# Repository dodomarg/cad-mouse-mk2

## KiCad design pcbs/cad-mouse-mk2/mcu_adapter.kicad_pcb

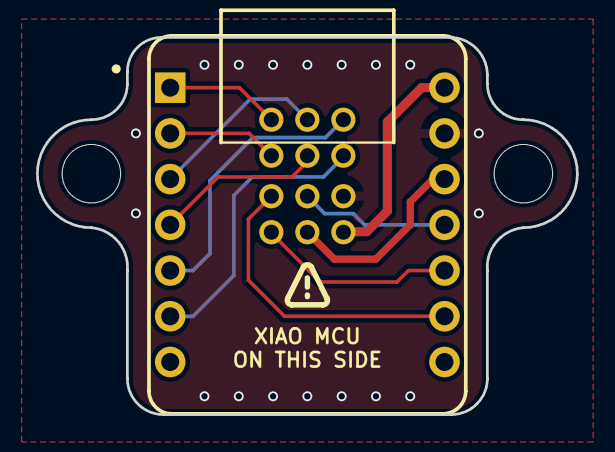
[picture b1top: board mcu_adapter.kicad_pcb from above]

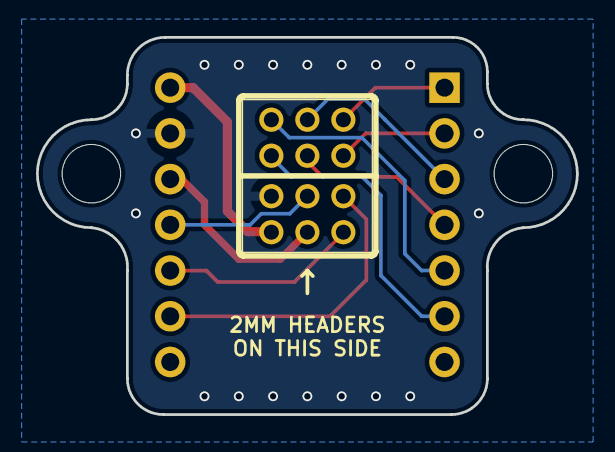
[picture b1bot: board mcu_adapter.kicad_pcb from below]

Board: 2 copper layers, 30.0 x 21.0 mm, 5 parts (2 on the bottom side), 12 nets.

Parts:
U1: XIAO-THRUHOLE; XIAO-GENERIC-THRUHOLE-MODULE14P-2.54-21X17.8MM_vf.79dh4xraR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
U$1, U$2: NRPN032PAEN-RC; CONN3X2_NRPN032PAEN-RC_vf.TnALXNQpQbKa17UGSM3jDw
UNK_HOLE_0: dummyfp0
UNK_HOLE_1: dummyfp1

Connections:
3V3: U1.12, U$2.3
5V: U1.14, U$2.1
D0: U1.1, U$1.6
D1: U1.2, U$1.5
D2: U1.3, U$1.4
D3: U1.4, U$1.3
D8: U1.9, U$2.6
D9: U1.10, U$2.5
D10: U1.11, U$2.4
GND: U1.13, U$2.2
SCL: U1.6, U$1.1
SDA: U1.5, U$1.2

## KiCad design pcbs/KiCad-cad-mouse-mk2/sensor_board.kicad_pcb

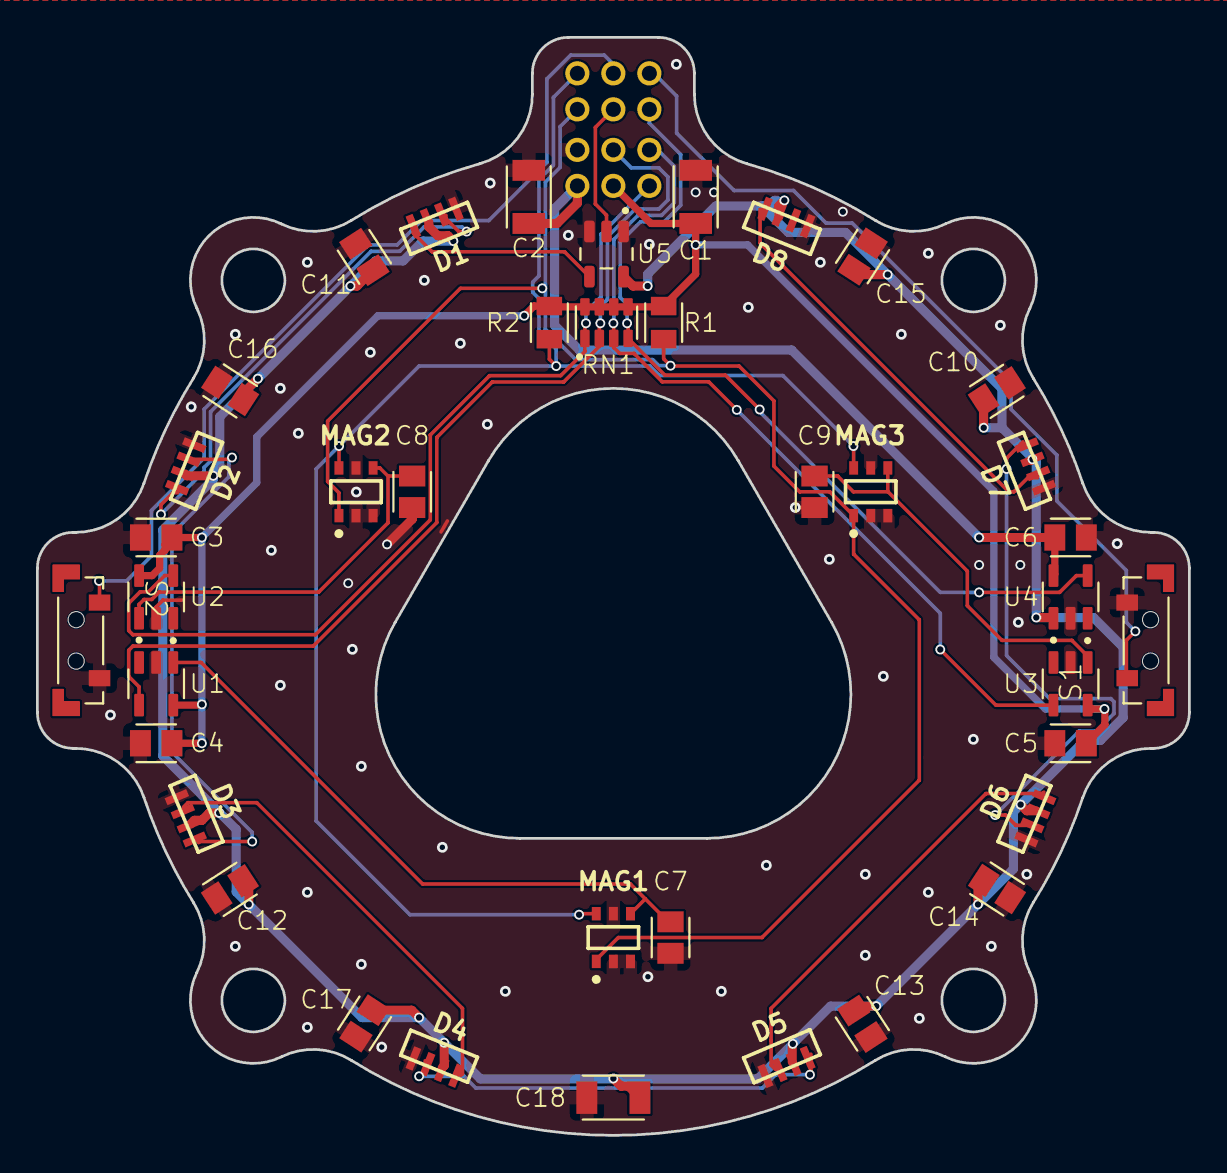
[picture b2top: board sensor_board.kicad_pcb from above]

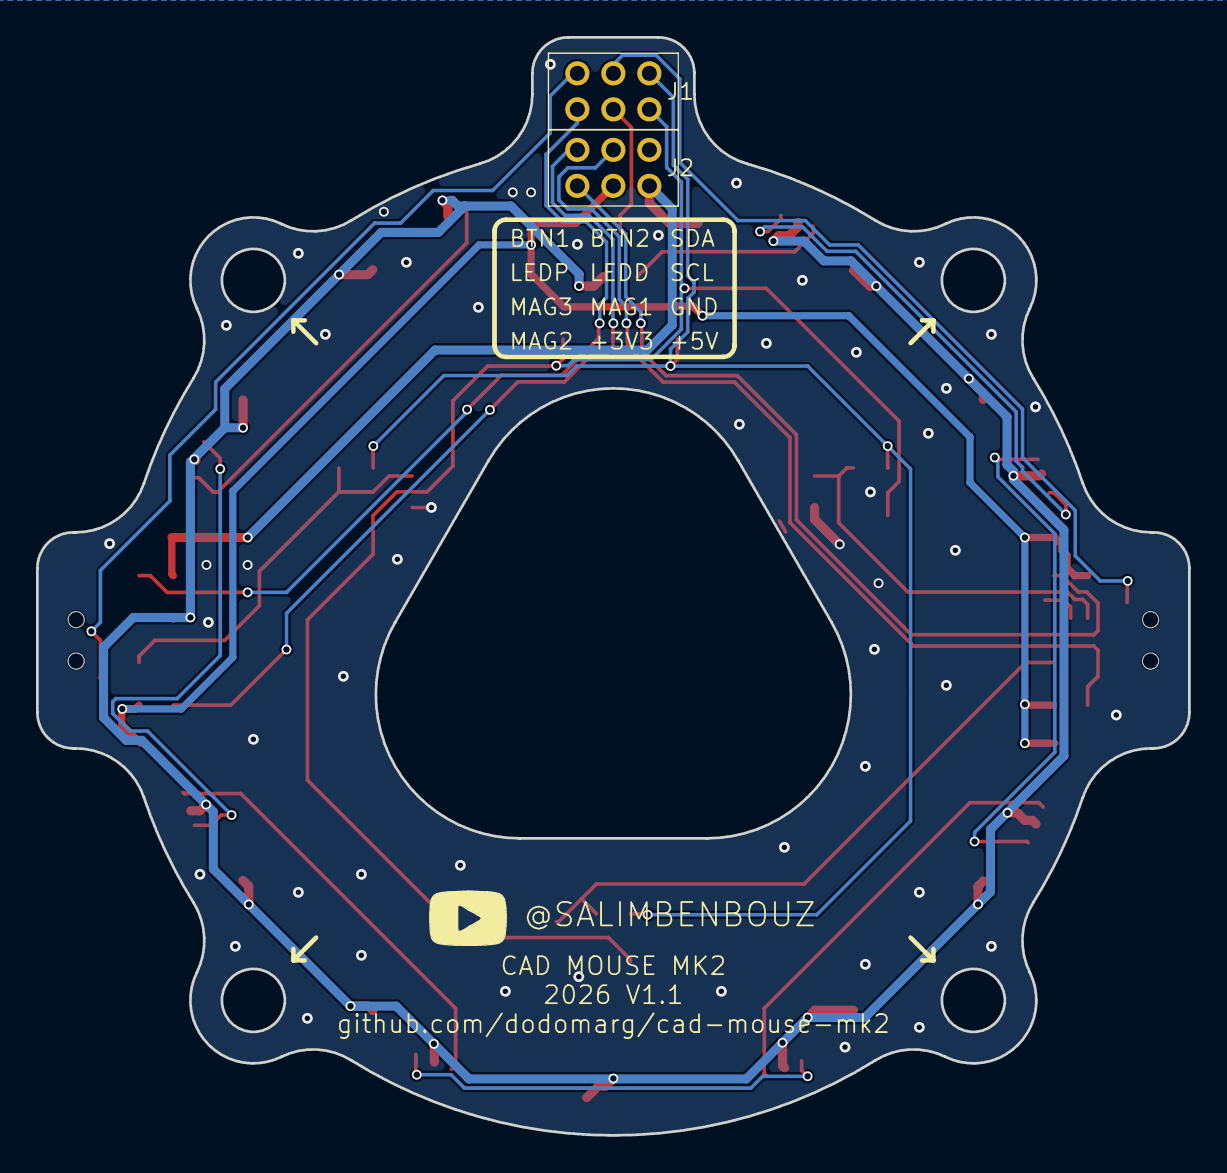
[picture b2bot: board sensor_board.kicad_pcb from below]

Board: 2 copper layers, 64.0 x 61.0 mm, 41 parts (2 on the bottom side), 24 nets.

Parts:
C1, C2: 1uF; CAPC3216X135_16290819
C3, C4, C5, C6, C7, C8, C9, C10, C11, C12, C13, C14, C15, C16, C17: 100nF; CAPC2012X110_16290819
C18: 22uF; CAPC3216X135_16290819
D1, D2, D3, D4, D5, D6, D7, D8: WS2812B-4020
J1, J2: CONN3X2_NPPN032AFCN-RC_SUL_vf.TnALXNQpQbKa17UGSM3jDw
MAG1, MAG2, MAG3: TLI493D-A2B6; SOP95P280X110-6N-V_vf.MgUPDs8QTrSiZWytZ2VEDw
R1, R2: 10K; RESC2012X65_16378527
RN1: 75R; RESCAF80P320X160X60-8N_vf.j0KZjKIVRhWMp-VC_KV2vA
S1, S2: Tactile TS32-7-35; TS32-7-35-BK-B-160-RA-SMT-TR
U1, U2, U4: AP22816BKEWT-7; SOT95P280X100-5N_vf.cdMrt1LeQPaWmu_AalG1Eg
U3: AP22817BKEWT-7; SOT95P280X100-5N_vf.cdMrt1LeQPaWmu_AalG1Eg
U5: SN74AHCT1G125DBVR; SOT95P280X145-5N_vf.s1_3h01YRRe2BlOdhheUSQ

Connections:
3V3: C1.2, C3.2, C4.2, C5.2, J2.3, R1.2, R2.2, RN1.5, RN1.6, RN1.7, RN1.8, U1.5 (IN), U2.5 (IN), U3.5 (IN)
5V: C2.2, C6.2, J2.5, U4.5 (IN)
/BTN_1: J1.5, S1.1
/BTN_2: J1.3, S2.1
/G_5V: C10.2, C11.2, C12.2, C13.2, C14.2, C15.2, C16.2, C17.2, C18.2, D1.2 (VDD), D2.2 (VDD), D3.2 (VDD), D4.2 (VDD), D5.2 (VDD), D6.2 (VDD), D7.2 (VDD), D8.2 (VDD), U4.1 (OUT), U5.5 (VCC)
/G_MAG1: C7.2, MAG1.4 (VDD), U1.1 (OUT)
/G_MAG2: C8.2, MAG2.4 (VDD), U2.1 (OUT)
/G_MAG3: C9.2, MAG3.4 (VDD), U3.1 (OUT)
/LED_DIN: D1.1 (DIN), U5.4 (Y)
/MCU_LED_DATA: J1.4, U5.2 (A)
/SCL: J1.2, MAG1.1 (SCL/INT), MAG2.1 (SCL/INT), MAG3.1 (SCL/INT), R1.1
/SDA: J1.1, MAG1.6 (SDA), MAG2.6 (SDA), MAG3.6 (SDA), R2.1
/~EN_LEDS: J1.6, RN1.4, U4.4 (~EN)
/~EN_MAG1: J2.4, RN1.2, U1.4 (~EN)
/~EN_MAG2: J2.1, RN1.1, U2.4 (~EN)
/~EN_MAG3: J2.2, RN1.3, U3.4 (~EN)
GND: C1.1, C2.1, C3.1, C4.1, C5.1, C6.1, C7.1, C8.1, C9.1, C10.1, C11.1, C12.1, C13.1, C14.1, C15.1, C16.1, C17.1, C18.1, D1.4 (GND), D2.4 (GND), D3.4 (GND), D4.4 (GND), D5.4 (GND), D6.4 (GND), D7.4 (GND), D8.4 (GND), J2.6, MAG1.2 (GND_1), MAG1.3 (GND_2), MAG1.5 (GND_3), MAG2.2 (GND_1), MAG2.3 (GND_2), MAG2.5 (GND_3), MAG3.2 (GND_1), MAG3.3 (GND_2), MAG3.5 (GND_3), S1.2, S2.2, U1.2 (GND), U2.2 (GND), U3.2 (GND), U4.2 (GND), U5.1 (~OE), U5.3 (GND)
unnamed: D1.3 (DOUT), D2.1 (DIN)
unnamed: D2.3 (DOUT), D3.1 (DIN)
unnamed: D3.3 (DOUT), D4.1 (DIN)
unnamed: D4.3 (DOUT), D5.1 (DIN)
unnamed: D5.3 (DOUT), D6.1 (DIN)
unnamed: D6.3 (DOUT), D7.1 (DIN)
unnamed: D7.3 (DOUT), D8.1 (DIN)

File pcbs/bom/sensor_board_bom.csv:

Reference Designators,LCSC Part Number,Manufacture Part Number,Manufacturer,Package,Description,Quantity,Datasheet,Board
"C3, C4, C5, C6, C7, C8, C9, C10, C11, C12, C13, C14, C15, C16, C17",C24497,CL31B104KBCNNNC,Samsung Electro-Mechanics,1206,100nF ±10% 50V Ceramic Capacitor X7R 1206,15,https://www.lcsc.com/datasheet/C24497.pdf?spm=wm.sxq.inf.ggs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,Sensor
"C1, C2",C318771,CL31B105KOFNNNE,Samsung Electro-Mechanics,1206,1uF ±10% 16V Ceramic Capacitor X7R 1206,2,https://www.lcsc.com/datasheet/C318771.pdf?spm=wm.sxq.inf.gg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,Sensor
C18,C7432786,HGC1206R5226M250NSPJ,Chinocera,1206,22uF ±20% 25V Ceramic Capacitor X5R 1206,1,https://www.lcsc.com/datasheet/C7432786.pdf?spm=wm.sxq.inf.g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,Sensor
"U1, U2, U3, U4",C6465520,AP22817BKEWT-7,DIODES,TSOT-23-5,"1 Active Low 1.5A High Side Switch TSOT-23-5 Power Distribution Switches, Load Drivers RoHS",4,https://www.lcsc.com/datasheet/C6465520.pdf?spm=wm.sxq.inf.g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,Sensor
"D1, D2, D3, D4, D5, D6, D7, D8",C965557,WS2812B-4020,Worldsemi,"SMD,4x2mm","SMD,4x2mm LED Addressable, Specialty RoHS",8,https://www.lcsc.com/datasheet/C965557.pdf?spm=wm.sxq.inf.gg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,Sensor
"MAG1, MAG2, MAG3",C1559664,TLI493DA2B6HTSA1,Infineon,TSOP-6-1.5mm,"TSOP-6-1.5mm Linear, Compass (ICs) RoHS",3,https://www.lcsc.com/datasheet/C1559664.pdf?spm=wm.sxq.inf.g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,Sensor
"R1, R2",C5159707,FRH0805B1002TS,FOJAN,805,10kΩ ±0.1% 125mW 0805 Thick Film Resistor,2,https://www.lcsc.com/datasheet/C5159707.pdf?spm=wm.sxq.inf.g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,Sensor
RN1,C784821,CAY16-103J4LF,BOURNS,0603x4,"4 ±5% 10kΩ 62.5mW ±200ppm/℃ 0603x4 Resistor Networks, Arrays RoHS",1,https://www.lcsc.com/datasheet/C784821.pdf?spm=wm.sxq.inf.gg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,Sensor
"S1, S2",C53202792,TS-1101U08-3x6x3.5-260,CAX,"SMD-4P,7x3.5mm","Without Bracket 7mm 12V 3.5mm Rectangular Button No SPST-NO 50mA SMD-4P,7x3.5mm Tactile Switches RoHS",2,https://www.lcsc.com/datasheet/C53202792.pdf?spm=wm.sxq.inf.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,Sensor
U5,C7484,SN74AHCT1G125DBVR,TI,SOT-23-5,"4.5V~5.5V 1 1 6.5ns@5V,15pF 10uA SOT-23-5 Buffers, Drivers, Receivers, Transceivers RoHS",1,https://www.lcsc.com/datasheet/C7484.pdf?spm=wm.sxq.inf.ggs_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,Sensor
"J1, J2",C49563339,A200UP-ZS03P-PC028,BXCONN,"Through Hole,P=2mm",Pin Header 6 Position Dual Row -40℃~+105℃,2,https://www.lcsc.com/datasheet/C49563339.pdf?spm=wm.sxq.inf.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,MCU
"H1, H2",C18723065,2005FV-2x3P,HanElectricity,"Through Hole,P=2mm",Female Header 6 Position 2mm Pitch Dual Row Through Hole -40℃~+105℃,2,https://www.lcsc.com/datasheet/C18723065.pdf?spm=wm.sxq.inf.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,Sensor

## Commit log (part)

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2026-06-14 partial kicad project
2026-06-14 re added missing kicad files
2026-06-14 added gerber files for jlcpcb based on new board alterations
2026-06-14 updated silk screen on sensor board pcb to link to the forked repo
2026-06-14 updated BOM files
2026-06-14 added FreeCAD files from https://github.com/relikd/cad-mouse-mk2-case-variations
2026-06-24 Adapt firmware to build and run on Seeed XIAO ESP32-S3
2026-06-28 Fix active-low load switches, custom HID descriptor, add I2C diagnostics
    - LED/sensor load switches are active-low (AP22817B): invert power logic
    - HID: register custom 6DoF descriptor in constructor so wDescriptorLength!=0
    - platformio: no_reset upload flags, monitor dtr/rts off, diag_i2c env
    - Ignore FreeCAD backups/exports
    - Add diag/ I2C scanner+address test (validated all 3 TLx493D sensors)
2026-06-30 Add config portal with persistent settings and telemetry CDC
    - Add Settings (NVS) for USB VID/PID and motion calibration persistence
    - Add ConfigPortal SoftAP web UI, entered by holding both buttons at boot
    - Route telemetry over TinyUSB-composited USBCDC alongside HID
    - Apply stored USB identity and calibration on startup
    - Update FreeCAD enclosure files and platformio.ini
